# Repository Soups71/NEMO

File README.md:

# NEMO Documentation

Welcome to NEMO—the **NMEA2000 Education and Maritime Operations Platform**.

NEMO is a research platform for exploring at maritime network security. It simulates sensors, sniffs traffic, and demonstrates just how easy you can mess with NMEA2000.

This platform focuses on lowering the bar for getting started with boat hacking. Typically to get started with boat hacking you would need thousands of dollars worth of equipment or a friend with a boat. Thankfully, with NEMO all you need is about 40 dollars.

## What's In Here

### Getting Your Feet Wet
1. **[Project Overview](Documentation/README.md)** - What this is and why boats need better security
2. **[Getting Started](Documentation/Getting_Started.md)** - From zero to flashing firmware
3. **[Operations Guide](Documentation/Operations_Guide.md)** - How to actually use the thing
4. **[FAQ](Documentation/FAQ.md)** - "Why doesn't X work?" answered here

### Understanding the Protocols
1. **[NMEA2000 Protocol](Documentation/NMEA2000.md)** - The marine standard for device communication

### Hardware
1. **[Design Reference](Documentation/PCB_Design.md)** - Schematics, layout, gerbers
2. **[3-D Printed Case](Documentation/Case_Design.md)** - Documentation on the case

### Software
9. **[Source Code Architecture](Documentation/Source_Code_Architecture.md)** - Deep dive into the firmware

### The Fun Part
10. **[Security Research & Attacks](Documentation/Attacks.md)** - How the attacks work and academic context

## Quick Start (TL;DR)

1. Get parts from [Hardware Guide](Documentation/PCB_Design.md)
2. Flash firmware via [Getting Started](Documentation/Getting_Started.md)
3. Learn the UI in [Operations Guide](Documentation/Operations_Guide.md)
4. Break Stuff
5. Profit!

## What This Is For

NEMO exists for:
- **Security researchers** exploring maritime vulnerabilities
- **Students** learning about CAN bus and protocol weaknesses
- **Industry folks** who want to see why NMEA2000 security matters

## Contributing

Found a bug? Got a cool feature idea? Open an issue or send a PR.

Contribution Ideas:
- New PGN support
- Bug fixes
- Documentation improvements

## Contact

Any questions or concerns regarding this project can be sent to nemo@jamescampbell.org

## Disclaimer

Released for educational and research purposes. Don't do crimes with it.

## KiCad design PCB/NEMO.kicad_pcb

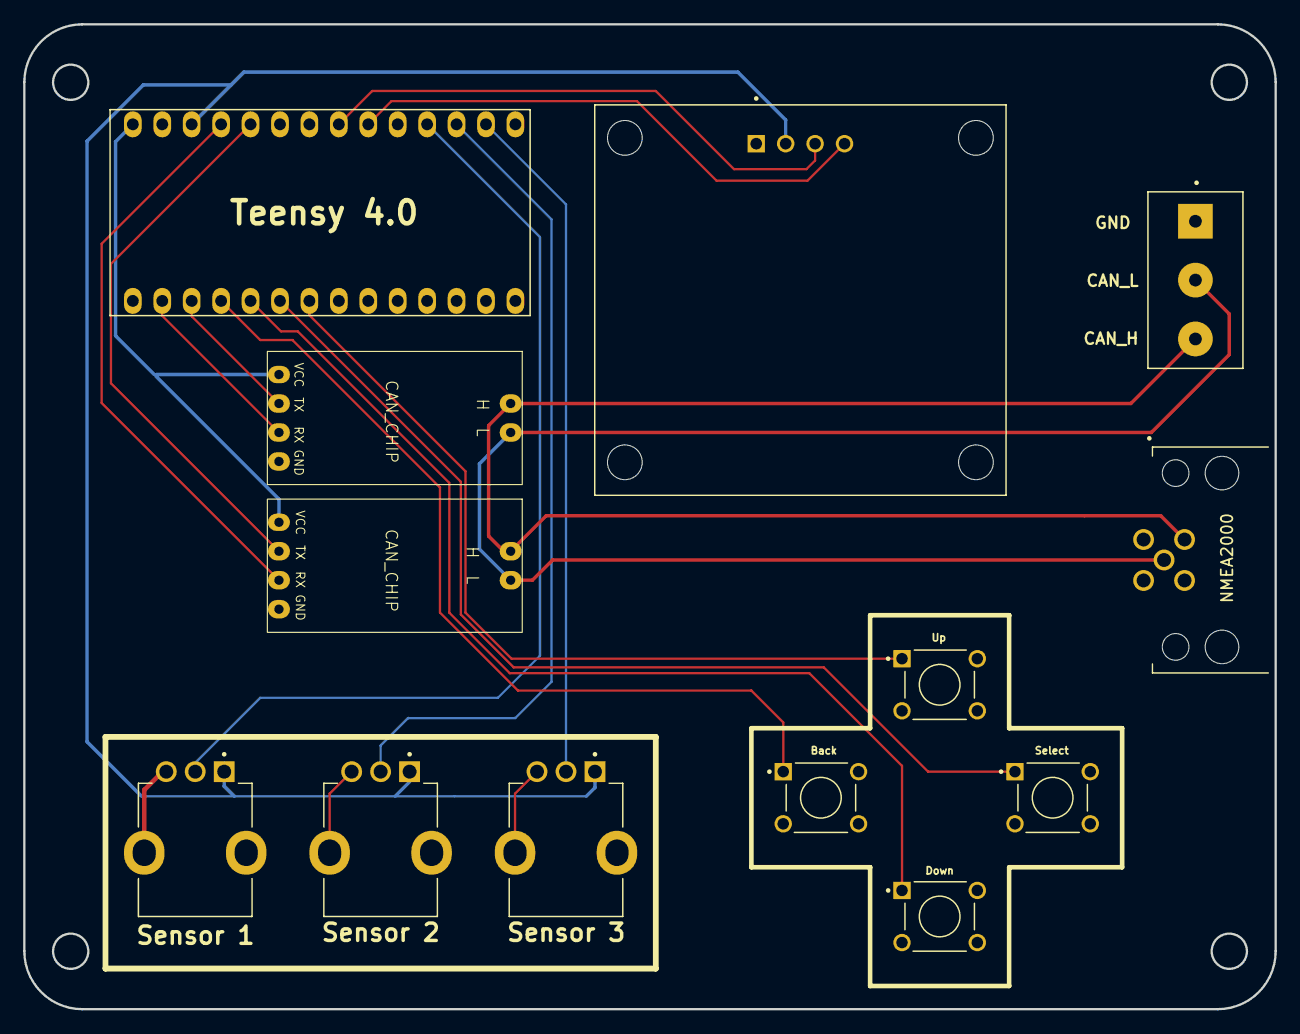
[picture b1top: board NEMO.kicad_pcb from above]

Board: 2 copper layers, 108.0 x 85.0 mm, 13 parts (0 on the bottom side), 18 nets.

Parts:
Back: 1825910-6; SW_1825910-6-4
DS1: OLED_128X64_1.3_I2C; LCD_OLED_128X64_1.3_I2C
Down: 1825910-6; SW_1825910-6-4
J1: 282837-3; TE_282837-3
NMEA2000: 54-00387; NMEA2000
R1, R2, R3: RV09AF-40-20K-A10K; TRIM_RV09AF-40-20K-A10K
Select: 1825910-6; SW_1825910-6-4
Teensy 4.0: DEV-15583; MODULE_DEV-15583
U2, U3: CAN_CHIP
Up: 1825910-6; SW_1825910-6-4

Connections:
+3.3V: DS1.2 (VDD), R1.1, R2.1, R3.1, Teensy 4.0.3.3V_2
+5V: Teensy 4.0.VIN, U2.1 (VCC), U3.1 (VCC)
CAN_1_rx: Teensy 4.0.23, U2.3 (RX)
CAN_1_tx: Teensy 4.0.22, U2.2 (TX)
CAN_2_rx: Teensy 4.0.0, U3.3 (RX)
CAN_2_tx: Teensy 4.0.1, U3.2 (TX)
CAN_H: J1.3, NMEA2000.4, U2.5 (CAN_HI), U3.5 (CAN_HI)
CAN_L: J1.2, NMEA2000.5, U2.6 (CAN_LOW), U3.6 (CAN_LOW)
GND: Back.3, DS1.1 (GND), Down.3, J1.1, NMEA2000.3, R1.3, R1.SH1 (SHIELD), R1.SH2 (SHIELD), R2.3, R2.SH1 (SHIELD), R2.SH2 (SHIELD), R3.3, R3.SH1 (SHIELD), R3.SH2 (SHIELD), Select.3, Teensy 4.0.G1, Teensy 4.0.G3, U2.4 (GND), U3.4 (GND), Up.3
SCK: DS1.3 (SCK), Teensy 4.0.19
SDA: DS1.4 (SDA), Teensy 4.0.18
button_1: Select.1, Teensy 4.0.4
button_2: Teensy 4.0.5, Up.1
button_3: Down.1, Teensy 4.0.3
button_4: Back.1, Teensy 4.0.2
pot_1: R1.2, Teensy 4.0.16
pot_2: R2.2, Teensy 4.0.15
pot_3: R3.2, Teensy 4.0.14

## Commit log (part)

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2026-01-25 First Release of NEMO
2026-02-17 Fixing broken links
